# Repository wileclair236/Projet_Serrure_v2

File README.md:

# Serrure Intelligente Connectée

## Description

Ce projet consiste en la conception et la réalisation d'une serrure intelligente connectée permettant le contrôle d'accès d'une porte à l'aide de plusieurs méthodes d'authentification. La serrure peut être commandée localement ou à distance via Home Assistant.

Le système est composé de plusieurs circuits imprimés (PCB) assurant la gestion des accès, les communications sans fil, l'acquisition d'images, le stockage des événements et le contrôle du mécanisme de verrouillage.

## Fonctionnalités

* Déverrouillage par carte RFID
* Déverrouillage par empreinte digitale
* Déverrouillage à distance via Home Assistant
* Déverrouillage mécanique par clé
* Notifications en temps réel
* Capture d'images lors des événements d'accès
* Journalisation des accès
* Gestion de plusieurs utilisateurs
* Contrôle d'un servomoteur pour le verrouillage et le déverrouillage
* Communication sans fil via Wi-Fi et MQTT

## Architecture du système

### PCB principal

Le PCB principal assure le contrôle complet de la serrure :

* Gestion des communications avec Home Assistant
* Gestion des utilisateurs autorisés
* Traitement des demandes d'accès
* Contrôle du servomoteur
* Acquisition et stockage des données
* Gestion des capteurs et périphériques

### PCB de la clé mécanique

Le PCB secondaire agit comme un interrupteur relié au PCB principal. Lorsqu'une clé est insérée puis tournée, il transmet un signal d'ouverture au contrôleur principal afin de permettre l'accès.

## Matériel utilisé

* ESP32-S3
* Lecteur RFID MFRC522
* Capteur d'empreintes digitales R503
* Caméra OV2640
* Écran OLED
* Servomoteur
* Carte microSD
* Capteur de proximité Vcnl36825t
* Batterie AA

## Logiciels utilisés

* PlatformIO
* Home Assistant
* MQTT
* Git
* KiCad

## Communication MQTT

Le système utilise MQTT pour transmettre les informations entre la serrure et Home Assistant.

## Sécurité

* Gestion des utilisateurs autorisés
* Journalisation des accès
* Authentification par plusieurs méthodes
* Surveillance des événements en temps réel
* Notifications automatiques vers Home Assistant

## Résultats

La serrure permet un contrôle d'accès sécurisé et connecté tout en conservant une solution de secours mécanique grâce à la clé physique. L'intégration avec Home Assistant offre une supervision en temps réel ainsi qu'une gestion centralisée des accès.

## Auteur

Wilkens Pinthière
Projet de conception d'une serrure intelligente connectée.

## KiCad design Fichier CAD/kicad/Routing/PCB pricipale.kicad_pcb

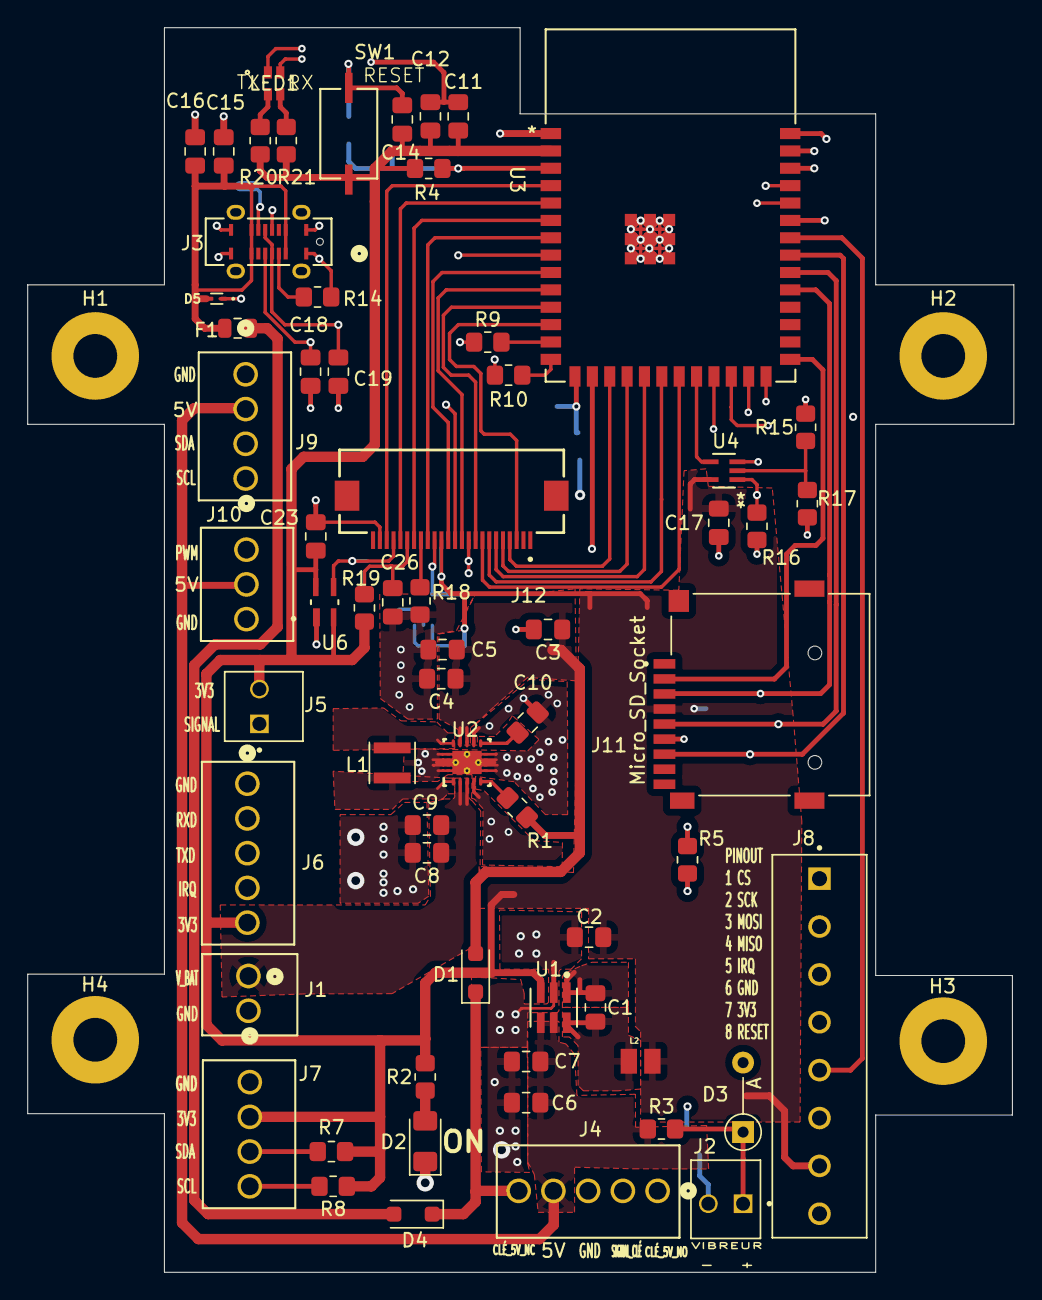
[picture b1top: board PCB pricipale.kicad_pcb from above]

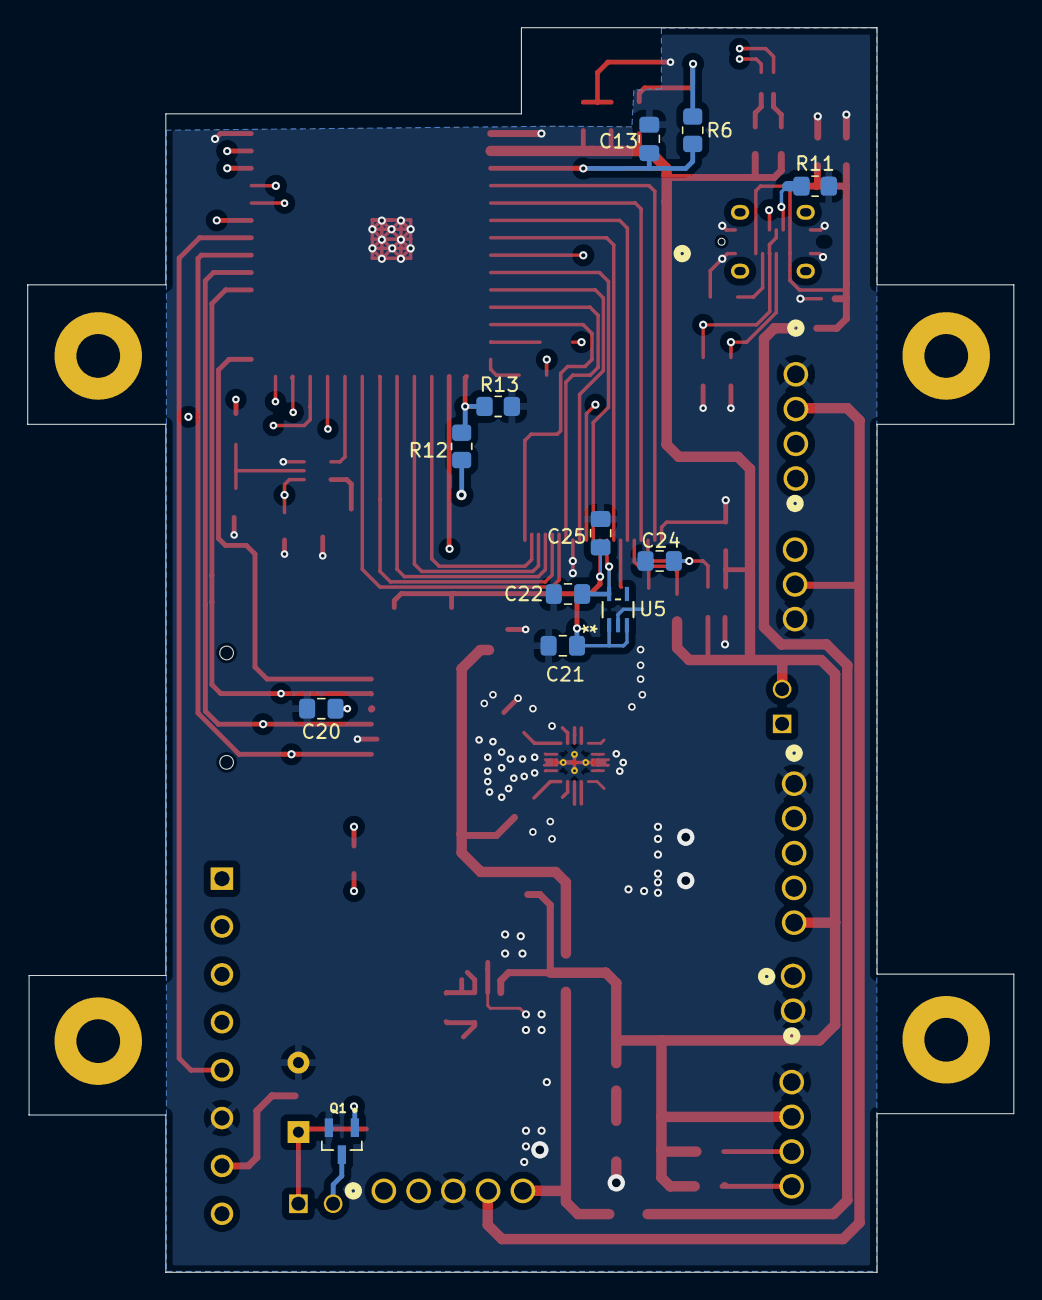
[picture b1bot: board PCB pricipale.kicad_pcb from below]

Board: 4 copper layers, 72.1 x 91.0 mm, 80 parts (12 on the bottom side), 66 nets.

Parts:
C1, C7, C10, C11, C13, C14, C16, C17, C20, C25, C26: 100n; C_0805_2012Metric_Pad1.18x1.45mm_HandSolder
C2, C8, C9, C15: 10u; C_0805_2012Metric_Pad1.18x1.45mm_HandSolder
C3, C4, C5, C12: 22u; C_0805_2012Metric_Pad1.18x1.45mm_HandSolder
C6, C21, C22, C23, C24: 1u; C_0805_2012Metric_Pad1.18x1.45mm_HandSolder
C18, C19: 0; C_0805_2012Metric_Pad1.18x1.45mm_HandSolder
D1, D4: D_Schottky; D_SOD-123F
D2: LED verte; LED_1206_3216Metric_Pad1.42x1.75mm_HandSolder
D3: 1N4148; D_DO-35_SOD27_P5.08mm_Vertical_AnodeUp
D5: D_TVS; SODFL1006X40N
F1: 1A; Fuse_0805_2012Metric
H1, H2, H3, H4: MountingHole; MountingHole_3.2mm_M3_Pad
J1: Vbat(6V a 5V); CONN_OSTVN02A150_OST
J2: Buzzer; TE_640456-2
J3: 2171820001; CONN_2171820001_MOL
J4: connecteur_clé; CONN5_516x256_OST
J5: SW_push; TE_640456-2
J6: R503; CONN5_516x256_OST
J7: proximité; CONN_OSTVN04A150_OST
J8: RFID; SAMESKY_TB0011-350-08GR
J9: Ecran; CONN_OSTVN04A150_OST
J10: Servo; CONN3_OSTVN03A150_OST
J11: Micro_SD_Socket; CUI_MSD-4-A
J12: CONNECTEUR CAM; GCT_FFC2B35-24-G_REVA2
L1: 1u; IND_LQH3NPN1R0MMEL
L2: 2.2/116mohms; INDC2016X120N
LED1: B2612UDNB05D000512U1930; SON4_PCB-261_HVK
Q1: MMBT3904-TP; SOT95P237X125-3N
R1: 1M; R_0805_2012Metric_Pad1.20x1.40mm_HandSolder
R2: 30; R_0805_2012Metric_Pad1.20x1.40mm_HandSolder
R3, R6, R9, R10: 0; R_0805_2012Metric_Pad1.20x1.40mm_HandSolder
R4, R7, R8, R15, R16: 10k; R_0805_2012Metric_Pad1.20x1.40mm_HandSolder
R5: 1k; R_0805_2012Metric_Pad1.20x1.40mm_HandSolder
R11, R14: 5.11k; R_0805_2012Metric_Pad1.20x1.40mm_HandSolder
R12: 470k; R_0805_2012Metric_Pad1.20x1.40mm_HandSolder
R13: 560k; R_0805_2012Metric_Pad1.20x1.40mm_HandSolder
R17: 20k; R_0805_2012Metric_Pad1.20x1.40mm_HandSolder
R18: 10K; R_0805_2012Metric_Pad1.20x1.40mm_HandSolder
R19: 4,7k; R_0805_2012Metric_Pad1.20x1.40mm_HandSolder
R20: 100; R_0805_2012Metric_Pad1.20x1.40mm_HandSolder
R21: 260; R_0805_2012Metric_Pad1.20x1.40mm_HandSolder
SW1: SW_Push; SW2_PTS636 SM25F SMTR LFS_CNK-M
U1: LMR50410Y3FQDBVRQ1; DBV0006A-IPC_B
U2: TPS63061DSCR; DSC0010E
U3: ESP32-S3-WROOM-1-N16R8; ESP32-S3-WROOM-1_EXP
U4: MC74HC1G32DFT1G; SC70-5_ONS
U5: NCP512SQ13T2G; SC-88A_ONS-M
U6: NCP662SQ28T1G; SC-82AB_ONS-M

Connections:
+2V8: C24.1, J12.21, U6.3 (VOUT)
+3.3V: C2.1, C11.1, C12.1, C14.1, C17.1, C20.1, C21.1, C23.1, C25.1, J5.2, J6.5, J7.2, J8.7, J11.4 (VDD), J12.14, L2.2, R2.2, R4.1, R7.1, R8.1, R19.2, R20.2, R21.2, SW1.1, U1.3 (FB), U3.2 (3V3), U4.5 (VCC), U5.1 (VIN), U5.3 (ENABLE), U6.2 (VIN), U6.4 (ENABLE)
+5V: C6.1, C7.1, J4.4, J9.2, J10.2, R3.1, U1.4 (EN), U1.5 (VIN)
+BATT: C8.1, C9.1, J1.1, R12.1, U2.2 (VIN), U2.3 (EN)
/+1V3: C22.1, J12.15, U5.5 (VOUT)
/ADC VBAT: R12.2, R13.1, U3.15 (IO3)
/Buzzer: R5.1, U3.16 (IO46)
/CC1: J3.A5 (CC1), R14.1
/CS_SD: J11.2 (CD/DAT3), U3.27 (IO0)
/Clé_NC_5V: D1.1 (K), D4.1 (K), J4.5
/D+: C19.1, J3.A6 (DP1), J3.B6 (DP2), R10.1
/D-: C18.1, J3.A7 (DN1), J3.B7 (DN2), R9.1
/EN: C13.1, R4.2, R6.2, U3.3 (EN)
/HREF: J12.16, U3.7 (IO7)
/INT_R503: J6.4, U3.26 (IO45)
/IO14: U3.22 (IO14), U4.4 (OUTY)
/IO47: J6.3, U3.24 (IO47)
/IO48: J6.2, U3.25 (IO48)
/IRQ RFID: J8.5, U3.34 (IO41)
/PCLK: J12.8, U3.21 (IO13)
/PWM Servo: J10.1, U3.23 (IO21)
/RFID_CS: J8.1, U3.35 (IO42)
/RXD: LED1.4, U3.36 (RXD0)
/SCL: J7.4, J9.4, R8.2, U3.38 (IO2)
/SDA: J7.3, J9.3, R7.2, U3.39 (IO1)
/SD_CLK(SCK): J8.2, J11.5 (CLK), U3.32 (IO39)
/SD_CMD(MOSI): J8.3, J11.3 (CMD), U3.31 (IO38)
/SD_DATA(MISO): J8.4, J11.7 (DAT0), U3.33 (IO40)
/SIO_C: J12.20, U3.5 (IO5)
/SIO_D: J12.22, U3.4 (IO4)
/Signal_clé: J4.2, R15.1
/TXD: LED1.1, U3.37 (TXD0)
/VSYNC: J12.18, U3.6 (IO6)
/Vout5V: C3.1, C4.1, C5.1, D1.2 (A), R1.1, U2.8 (FB), U2.9 (VOUT)
/XCLK: J12.12, U3.8 (IO15)
/Y2: J12.6, U3.19 (IO11)
/Y3: J12.4, U3.17 (IO9)
/Y4: J12.3, U3.12 (IO8)
/Y5: J12.5, U3.18 (IO10)
/Y6: J12.7, U3.20 (IO12)
/Y7: J12.9, U3.11 (IO18)
/Y8: J12.11, U3.10 (IO17)
/Y9: J12.13, U3.9 (IO16)
GND: C2.2, C3.2, C4.2, C5.2, C6.2, C7.2, C8.2, C9.2, C10.2, C11.2, C12.2, C13.2, C15.2, C16.2, C17.2, C18.2, C19.2, C20.2, C21.2, C22.2, C23.2, C24.2, C25.2, C26.2, D2.1 (K), D3.2 (A), D5.1, J1.2, J3.A1 (GND), J3.A12 (GND), J3.B1 (GND), J3.B12 (GND), J4.3, J6.1, J7.1, J8.6, J9.1, J10.3, J11.6 (VSS), J12.10, J12.23, Q1.2, R11.2, R13.2, R14.2, R16.1, R17.2, R18.2, U1.2 (GND), U2.4 (PS_SYNC), U2.7 (GND), U2.11 (PAD), U3.1 (GND), U3.40 (GND), U3.41 (GND), U3.46 (GND), U3.47 (GND), U3.48 (GND), U3.49 (GND), U4.3 (GND), U5.2 (GND), U6.1 (GND)
unnamed: C14.2, R6.1, SW1.2
unnamed: C26.1, J12.19, R19.1
unnamed: D2.2 (A), R2.1
unnamed: D3.1 (K), J2.1, R3.2
unnamed: D4.2 (A), F1.2
unnamed: J2.2, Q1.3
unnamed: J3.B5 (CC2), R11.1
unnamed: J12.17, R18.1
unnamed: LED1.2, R20.1
unnamed: LED1.3, R21.1
unnamed: Q1.1, R5.2
unnamed: C1.2, U1.1 (CB)
unnamed: C1.1, L2.1, U1.6 (SW)
unnamed: L1.2, U2.1 (L1)
unnamed: L1.1, U2.10 (L2)
unnamed: R1.2, U2.5 (PG)
unnamed: C10.1, U2.6 (VAUX)
unnamed: R9.2, U3.13 (IO19)
unnamed: R10.2, U3.14 (IO20)
unnamed: R15.2, R17.1, U4.2 (INA)
unnamed: J5.1, R16.2, U4.1 (INB)
VBUS: C15.1, C16.1, D5.2, F1.1, J3.A4 (VBUS), J3.A9 (VBUS), J3.B4 (VBUS), J3.B9 (VBUS)

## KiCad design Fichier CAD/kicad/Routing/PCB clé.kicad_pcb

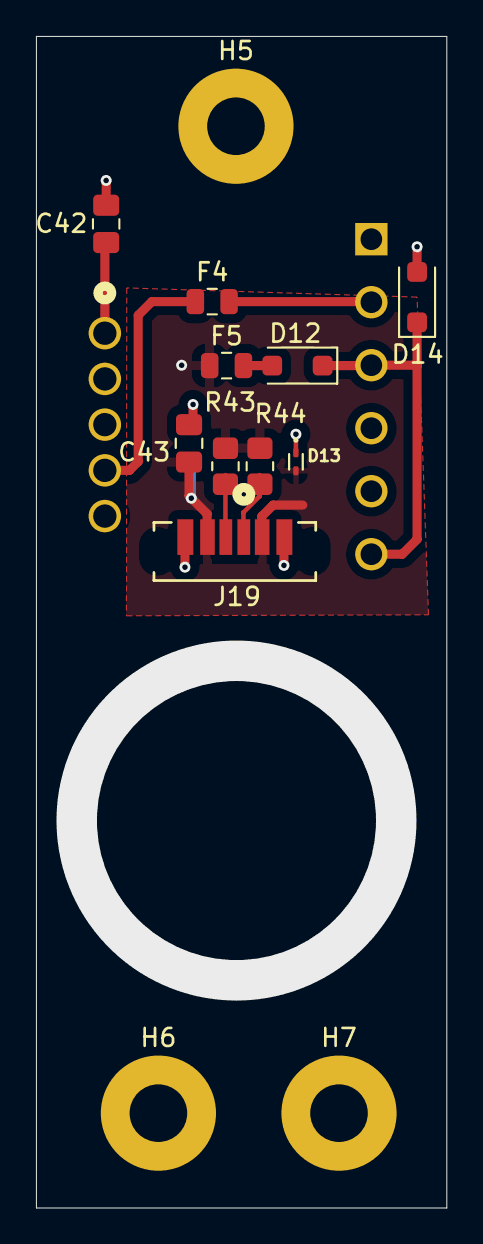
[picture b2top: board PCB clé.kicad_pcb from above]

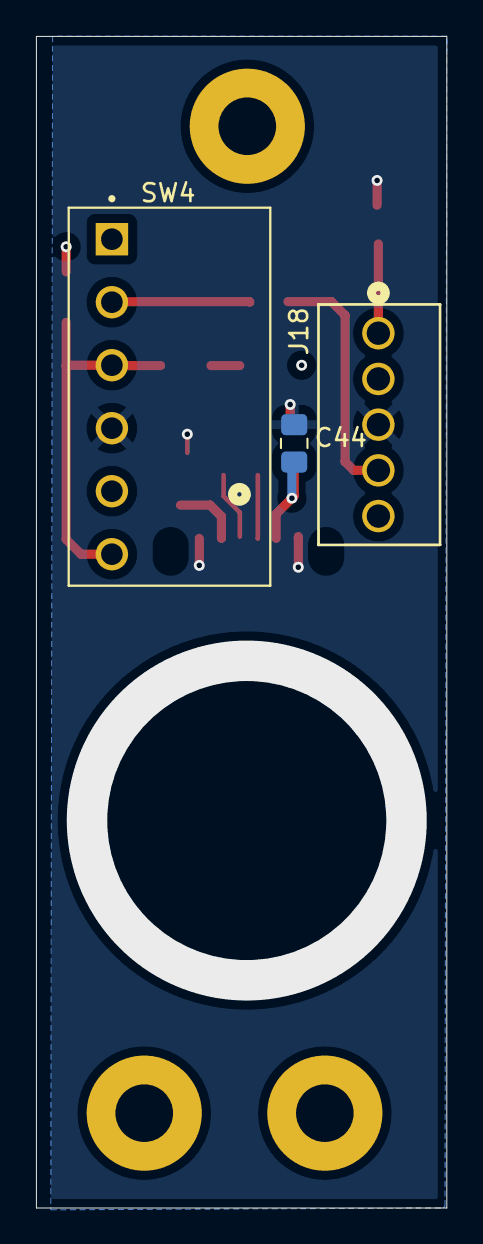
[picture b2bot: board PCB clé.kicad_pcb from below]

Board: 4 copper layers, 22.8 x 65.1 mm, 16 parts (3 on the bottom side), 11 nets.

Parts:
C42, C43: 10u; C_0805_2012Metric_Pad1.18x1.45mm_HandSolder
C44: 100n; C_0805_2012Metric_Pad1.18x1.45mm_HandSolder
D12, D14: D_Schottky; D_SOD-123F
D13: D_TVS; SODFL1006X40N
F4, F5: 1A; Fuse_0805_2012Metric
H5, H6, H7: MountingHole; MountingHole_3.2mm_M3_Pad
J18: Connecteur_PCB Clé; CONN5_516x256_OST
J19: 2171780001; CONN_2171780001_MOL
R43, R44: 56k; R_0805_2012Metric_Pad1.20x1.40mm_HandSolder
SW4: SW_CLÉ; PHOENIX_1988998

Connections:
+5V: F4.1, J18.4
/PCB_autre/Clé_NC_5V: J18.5, SW4.1 (A)
/PCB_autre/Clé_NO_5V: D12.1 (K), D14.1 (K), SW4.3 (C), SW4.6 (C)
/PCB_autre/Clé_NO_5V_urg: C42.1, D14.2 (A), J18.1
/PCB_autre/Signal_clé_2: J18.2, SW4.5 (B)
/PCB_autre/VBUS_PWR_URG: C43.1, C44.1, D13.2, F5.1, J19.A9 (VBUS), J19.B9 (VBUS), R43.2, R44.2
GND2: C42.2, C43.2, C44.2, D13.1, J18.3, J19.A12 (GND), J19.B12 (GND), SW4.4 (A)
unnamed: D12.2 (A), F5.2
unnamed: F4.2, SW4.2 (B)
unnamed: J19.A5 (CC1), R44.1
unnamed: J19.B5 (CC2), R43.1

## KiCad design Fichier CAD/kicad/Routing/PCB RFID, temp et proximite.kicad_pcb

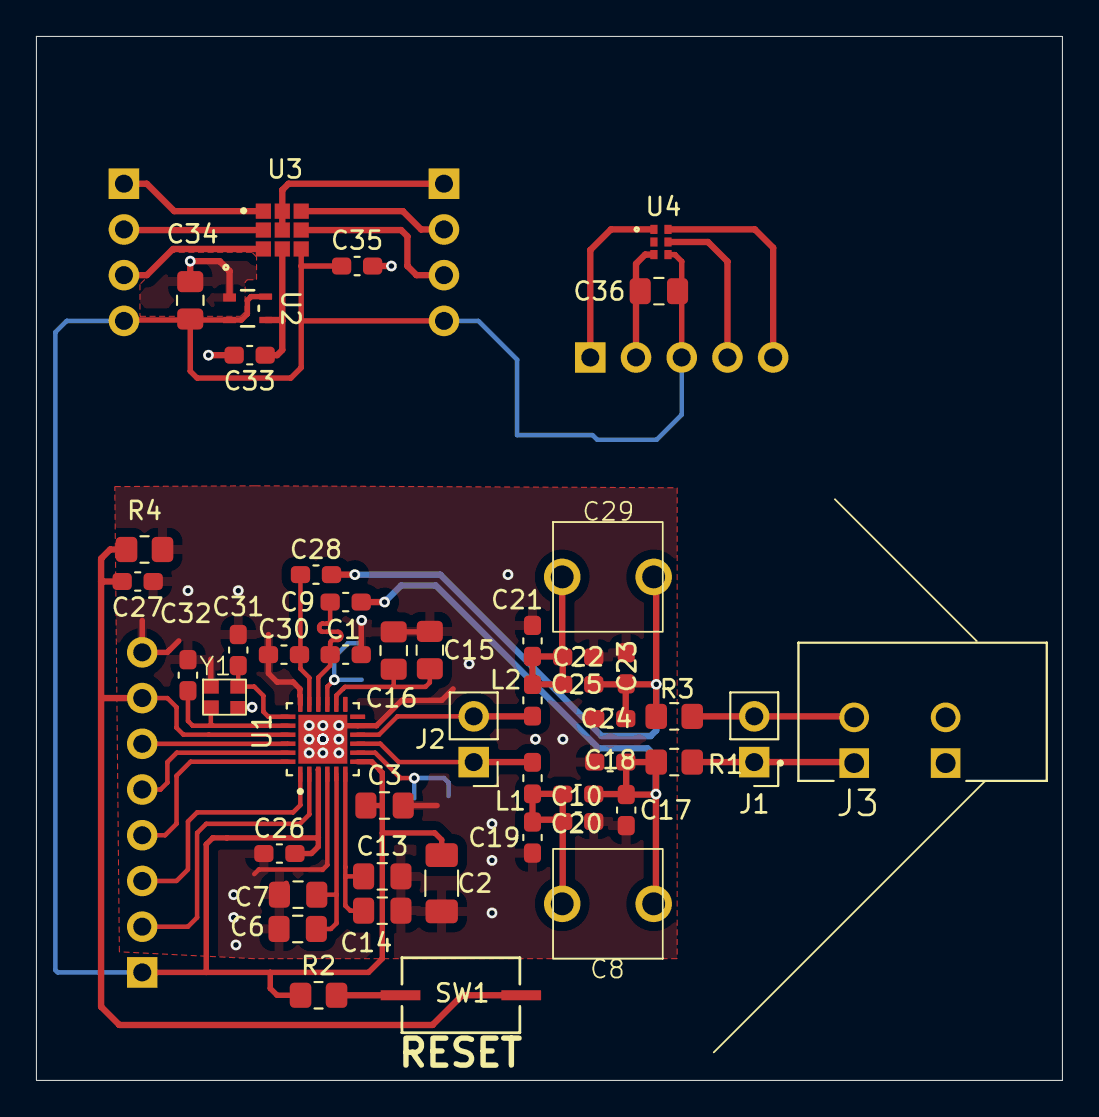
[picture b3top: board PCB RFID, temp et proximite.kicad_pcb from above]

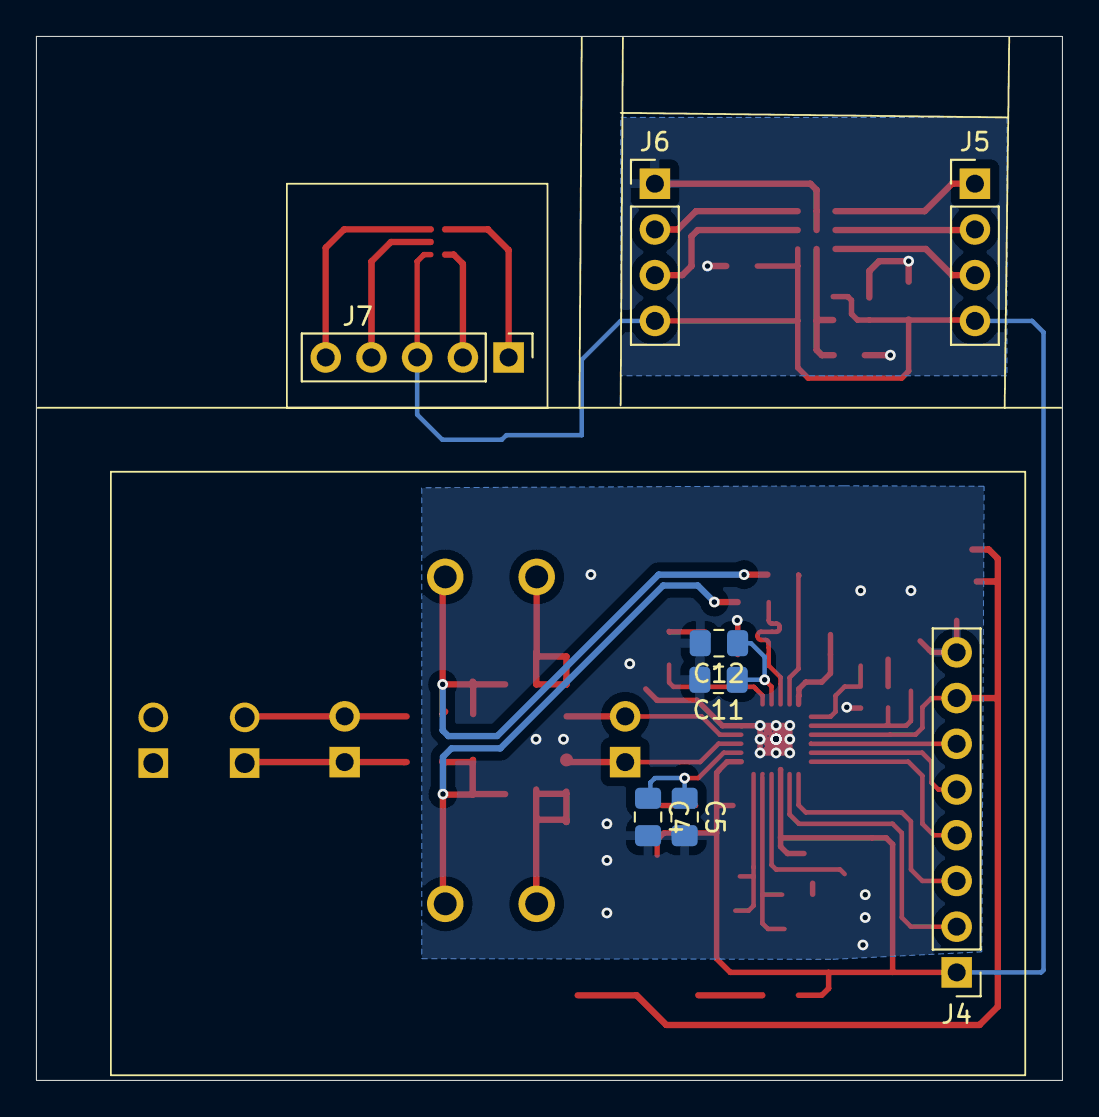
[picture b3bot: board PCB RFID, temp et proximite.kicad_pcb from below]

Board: 2 copper layers, 57.0 x 58.0 mm, 55 parts (8 on the bottom side), 37 nets.

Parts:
C1, C30: 150p; C_0603_1608Metric_Pad1.08x0.95mm_HandSolder
C2: 4.7u; C_1206_3216Metric_Pad1.33x1.80mm_HandSolder
C3, C4, C6, C12, C13, C15: 10n; C_0805_2012Metric_Pad1.18x1.45mm_HandSolder
C5, C7, C14, C16: 2.2u; C_0805_2012Metric_Pad1.18x1.45mm_HandSolder
C8, C29: 3-10p; C_TRIM
C9, C28: 10p; C_0603_1608Metric_Pad1.08x0.95mm_HandSolder
C10, C25: 30; C_0603_1608Metric_Pad1.08x0.95mm_HandSolder
C11, C34, C36: 1u; C_0805_2012Metric_Pad1.18x1.45mm_HandSolder
C17, C23: 68p; C_0603_1608Metric_Pad1.08x0.95mm_HandSolder
C18, C24: 20p; C_0603_1608Metric_Pad1.08x0.95mm_HandSolder
C19, C21: 220p; C_0603_1608Metric_Pad1.08x0.95mm_HandSolder
C20, C22: 15p; C_0603_1608Metric_Pad1.08x0.95mm_HandSolder
C26, C27, C33, C35: 100n; C_0603_1608Metric_Pad1.08x0.95mm_HandSolder
C31, C32: 13p; C_0603_1608Metric_Pad1.08x0.95mm_HandSolder
J1, J2: testpoint; PinHeader_1x02_P2.54mm_Vertical
J3: CONN_ANT; CUI_TBL003-254-02GR-2OR
J4: pin RFID; PinHeader_1x08_P2.54mm_Vertical
J5: pin droit; PinHeader_1x04_P2.54mm_Vertical
J6: pin gauche; PinHeader_1x04_P2.54mm_Vertical
J7: pin proxi; PinHeader_1x05_P2.54mm_Vertical
L1, L2: 270n; L_0603_1608Metric_Pad1.05x0.95mm_HandSolder
R1, R3: 1.6; R_0805_2012Metric_Pad1.20x1.40mm_HandSolder
R2: 10k; R_0805_2012Metric_Pad1.20x1.40mm_HandSolder
R4: 330k; R_0805_2012Metric_Pad1.20x1.40mm_HandSolder
SW1: SW_Push; SW2_PTS636 SM25F SMTR LFS_CNK-M
U1: ST25R100-CMET; QFN50P400X400X60-25N
U2: NCP562SQ18T1G; SC-82AB_ONS-L
U3: ENS160-BGLM; XDCR_ENS160-BGLM
U4: VCNL36825T; SMT_L36825T_VIS
Y1: Crystal_GND24; CRYSTAL_27.12MHZ

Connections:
+3.3V: C2.1, C3.1, C26.1, C34.1, C35.1, C36.2, J4.1, J5.4, J6.4, J7.3, R2.1, U1.3 (VDD_IO), U1.7 (VDD), U2.2 (VIN), U2.4 (ENABLE), U3.5 (VDDIO), U4.4 (VDD)
/AGD: C11.1, C12.1, U1.15 (AGD)
/EMC_N: C21.2, C22.2, C25.1, C29.1, L2.2
/EMC_P: C8.2, C10.1, C19.1, C20.1, L1.2
/FILTRE_N: C23.2, C24.1, C25.2, C28.2, C29.2, R3.1
/FILTRE_P: C8.1, C9.1, C10.2, C17.2, C18.2, R1.1
/RANT_N: J1.2, J3.2_A (2), R3.2
/RANT_P: J1.1, J3.1_A (1), R1.2
/RESET: C27.2, J4.7, R4.2, SW1.2, U1.21 (RESET)
/RFI1: C1.1, C9.2, U1.16 (RFI1)
/RFI2: C28.1, C30.2, U1.17 (RFI2)
/RFO1: J2.1, L1.1, U1.9 (RFO1)
/RFO2: J2.2, L2.1, U1.10 (RFO2)
/VDD_A: C15.1, C16.1, U1.14 (VDD_A)
/VDD_AM: C13.1, C14.1, U1.6 (VDD_AM)
/VDD_D: C6.1, C7.1, U1.5 (VDD_D)
/VDD_DR: C4.1, C5.1, U1.8 (VDD_DR)
/pcb TEMP/~CS: J6.2, U3.7 (~CS)
/pcb TEMP/~INT: J6.3, U3.6 (~INT)
/proximité/SCL_0: J7.4, U4.5 (SCL)
/proximité/SDA_0: J7.5, U4.6 (SDA)
GND: C1.2, C2.2, C3.2, C4.2, C5.2, C6.2, C7.2, C11.2, C12.2, C13.2, C14.2, C15.2, C16.2, C17.1, C18.1, C19.2, C20.2, C21.1, C22.1, C23.1, C24.2, C26.2, C27.1, C30.1, C31.2, C32.2, J4.8, R4.1, U1.4 (GND_D), U1.11 (GND_DR), U1.18 (GND_A), U1.25 (VSS), Y1.2, Y1.4
GND1: C33.2, C34.2, C35.2, J6.1, U2.1 (GND), U3.8 (VSS), U3.9 (VSS__1)
GND2: C36.1, J7.2, U4.3 (GND)
unnamed: J4.2, U1.2 (MISO)
unnamed: J4.3, U1.1 (IRQ)
unnamed: J4.4, U1.24 (SCLK)
unnamed: J4.5, U1.23 (MOSI)
unnamed: J4.6, U1.22 (~BSS)
unnamed: J5.1, U3.1 (MOSI/SDA)
unnamed: J5.2, U3.2 (SCLK/SCL)
unnamed: J5.3, U3.3 (MISO/ADDR)
unnamed: J7.1, U4.1 (INT)
unnamed: R2.2, SW1.1
unnamed: C31.1, U1.19 (XTI), Y1.3
unnamed: C32.1, U1.20 (XTO), Y1.1
unnamed: C33.1, U2.3 (VOUT), U3.4 (VDD)

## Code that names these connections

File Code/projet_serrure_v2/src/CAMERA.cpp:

#include "camera.h"
#include <Arduino.h>

camera_config_t config;

void camera_setup()
{
    Serial.println("Initialisation de la caméra...");
    // camera
    config.ledc_channel = LEDC_CHANNEL_0;
    config.ledc_timer = LEDC_TIMER_0;
    config.pin_d0 = Y2_GPIO_NUM;
    config.pin_d1 = Y3_GPIO_NUM;
    config.pin_d2 = Y4_GPIO_NUM;
    config.pin_d3 = Y5_GPIO_NUM;
    config.pin_d4 = Y6_GPIO_NUM;
    config.pin_d5 = Y7_GPIO_NUM;
    config.pin_d6 = Y8_GPIO_NUM;
    config.pin_d7 = Y9_GPIO_NUM;
    config.pin_xclk = XCLK_GPIO_NUM;
    config.pin_pclk = PCLK_GPIO_NUM;
    config.pin_vsync = VSYNC_GPIO_NUM;
    config.pin_href = HREF_GPIO_NUM;
    config.pin_sccb_sda = SIOD_GPIO_NUM;
    config.pin_sccb_scl = SIOC_GPIO_NUM;
    config.pin_pwdn = PWDN_GPIO_NUM;
    config.pin_reset = RESET_GPIO_NUM;
    config.xclk_freq_hz = 20000000;
    config.frame_size = FRAMESIZE_QVGA;
    config.pixel_format = PIXFORMAT_JPEG; // for streaming
    config.grab_mode = CAMERA_GRAB_WHEN_EMPTY;
    config.fb_location = CAMERA_FB_IN_PSRAM;
    config.jpeg_quality = 12; // 0-63 lower number means higher quality
    config.fb_count = 1;

    if (psramFound())
    {
        if (config.jpeg_quality < 10)
        {
            config.jpeg_quality = 10;
        }
        config.fb_count = 2;
        config.grab_mode = CAMERA_GRAB_LATEST;
    }
    else
    {
        if (config.jpeg_quality < 10)
        {
            config.jpeg_quality = 10;
        }
        config.frame_size = FRAMESIZE_QVGA;
        config.fb_location = CAMERA_FB_IN_DRAM;
    }

    esp_err_t err = esp_camera_init(&config);
    if (err != ESP_OK)
    {
        Serial.printf("Camera init failed with error 0x%x", err);
        return;
    }

    // Sensor settings
    sensor_t *s = esp_camera_sensor_get();
    if (s) {
        s->set_brightness(s, 1);
        s->set_contrast(s, 1);
        s->set_saturation(s, 1);
        s->set_whitebal(s, 1);
        s->set_awb_gain(s, 1);
        s->set_exposure_ctrl(s, 1);
        s->set_aec2(s, 1);
        s->set_vflip(s, 0);
    }

    Serial.println("Camera setup terminé.");
}

void capture_picture()
{
    // Capture d'image
    camera_fb_t *fb = esp_camera_fb_get();
    if (!fb)
    {
        Serial.println("Échec de la capture de l'image");
        return;
    }

    // Traiter l'image capturée (par exemple, l'envoyer via MQTT, la sauvegarder sur la carte SD, etc.)
    Serial.println("Image capturée avec succès, taille: " + String(fb->len) + " octets");
    esp_camera_fb_return(fb);
}

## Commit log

2026-05-29 ajout code et image
2026-05-29 Ajout projet_serrure_v2
2026-05-29 Update README title for version 2
2026-05-29 Ajout kicad et python
2026-05-29 ajout photo
2026-05-29 ajout video et stl
2026-05-29 ajout photo serrure
2026-05-29 ajout photo serrure2
2026-06-01 31/5/26 changement
2026-06-01 changement image schema principle
2026-06-01 changement image schema principle2
2026-06-01 image pcb
2026-06-01 Readme
    Added detailed project description, features, system architecture, hardware and software used, MQTT communication, security measures, results, and author information.
2026-06-01 image pcb2
